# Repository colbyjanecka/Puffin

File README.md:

<p align="center">

<br><br></p>

# Puffin Keys - Mechanical Keyboard / MIDI Sequencer

*The Atlantic Puffin is not just any bird.*

It's a skilled flier, reaching speeds of 88km/h by flapping their wings up to 400 per minute.  They are also expert swimmers, diving up to 60 meters while using their wings to propel themselves through  water.

**Here, we have the Puffin of Mechanical Keyboards.**  

First, the Puffin Keys is an exceptional typer.  By utilizing low profile mechanical switches, it creates a fun and exception typing experience in a small portable package. 

Second, it serves as a powerful MIDI controller and sequencer that can communicate both wirelessly and the onboard TRS hardware jacks.

[**`Powered by Mania Synths`**](https://mania.fm/)

## Features

- Kailh Choc v1 Switches with Hotswap Sockets
- Per-Key RGB Backlighting with SK6812 LEDs
- 2 x TRS Type-A MIDI Jacks (In and Out)
- 3000 mAh LIPO Battery
- Bluetooth 5 and BLE 
- Dual 32bit Xtensa LX7 cores
- 0.91" OLED Display*
- Future Expansion Capabilities

**The screen can be replaced with alternative I2C input/output modules such as knobs, sensors, or CV ports.*

## PCB

<p align="center">
<br><h3> Front</h3>

<br><h3> Back</h3>

<br><br></p>

## Layout

<p align="center">
<br><h3> Front</h3>

<br><h3> Back</h3>

<br><br></p>

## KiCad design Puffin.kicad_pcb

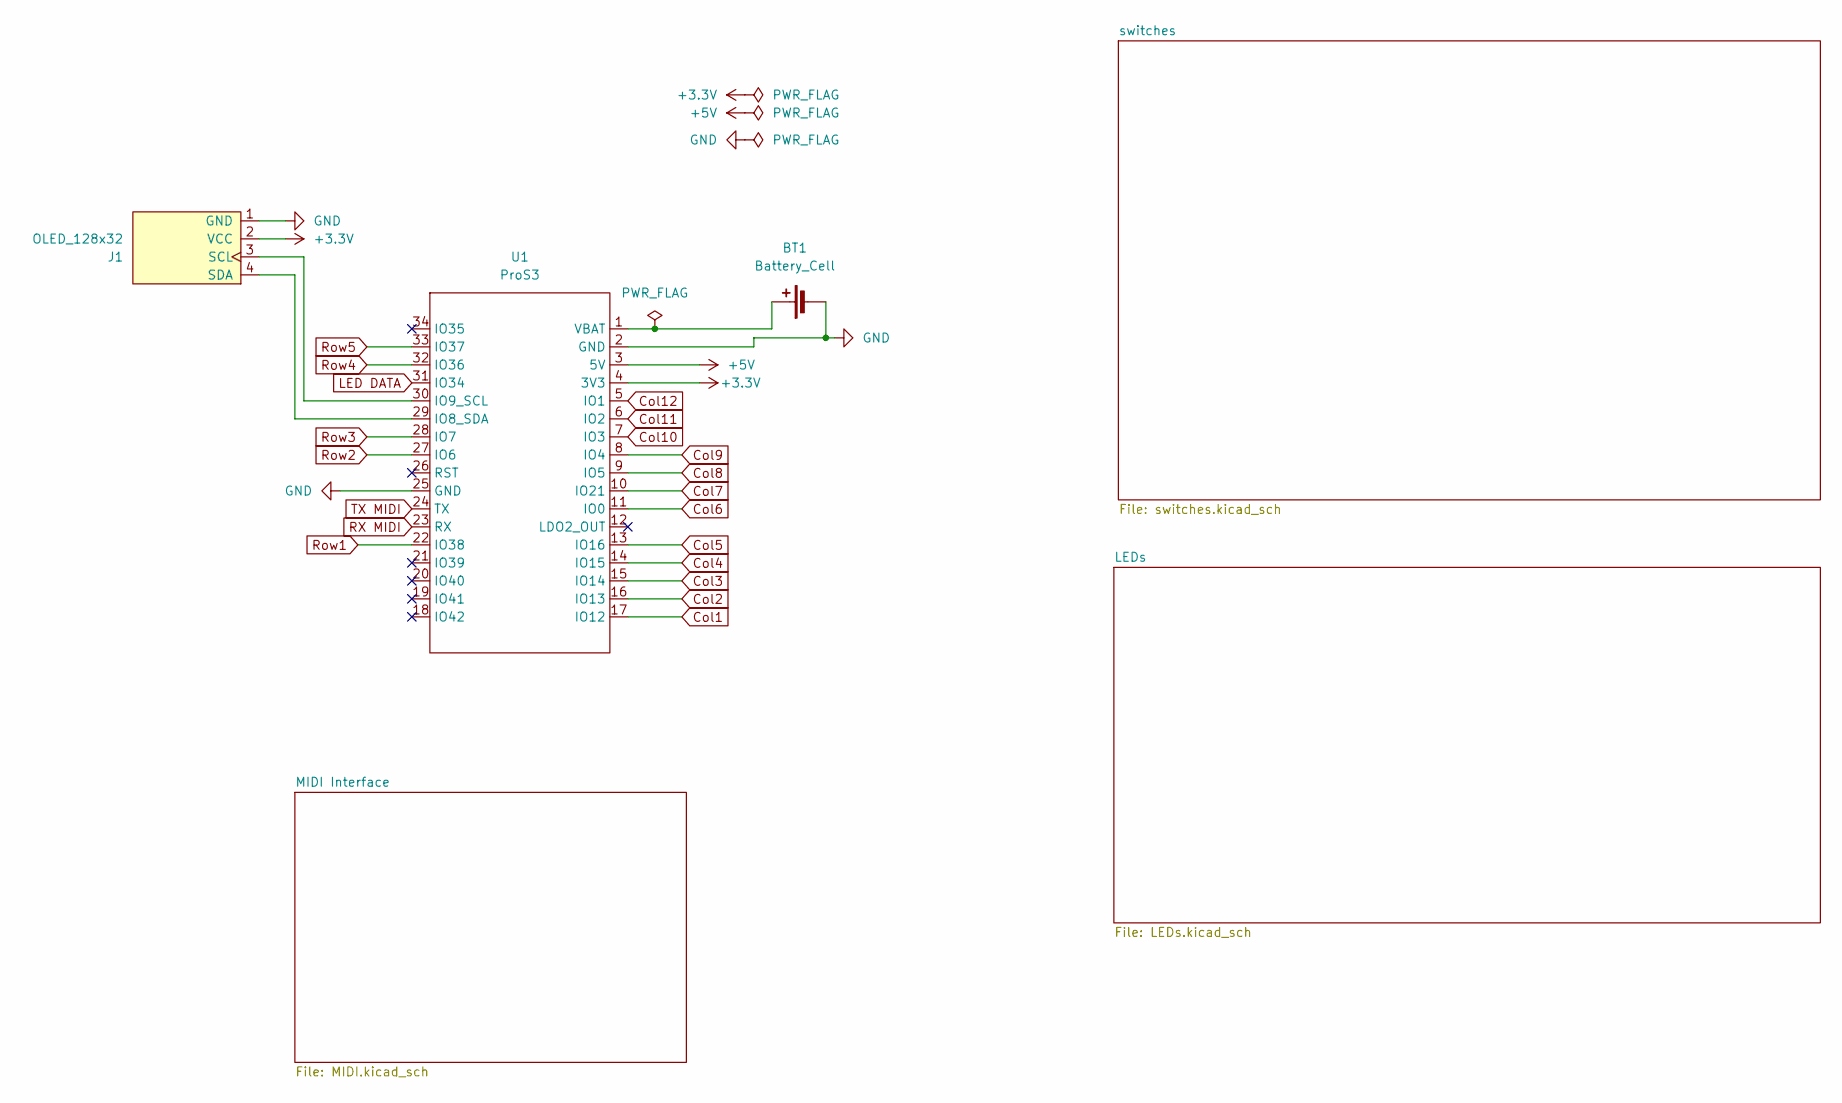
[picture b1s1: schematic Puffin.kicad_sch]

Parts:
BT1: Battery_Cell
J1: OLED_128x32
U1: ProS3; ProS3_TH

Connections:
+3.3V: J1.2 (VCC), U1.4 (3V3)
+5V: U1.3 (5V); also elsewhere on the board
Col1: U1.17 (IO12); also elsewhere on the board
Col2: U1.16 (IO13); also elsewhere on the board
Col3: U1.15 (IO14); also elsewhere on the board
Col4: U1.14 (IO15); also elsewhere on the board
Col5: U1.13 (IO16); also elsewhere on the board
Col6: U1.11 (IO0); also elsewhere on the board
Col7: U1.10 (IO21); also elsewhere on the board
Col8: U1.9 (IO5); also elsewhere on the board
Col9: U1.8 (IO4); also elsewhere on the board
Col10: U1.7 (IO3); also elsewhere on the board
Col11: U1.6 (IO2); also elsewhere on the board
Col12: U1.5 (IO1); also elsewhere on the board
GND: BT1.2 (-), J1.1 (GND), U1.2 (GND), U1.25 (GND); also elsewhere on the board
LED DATA: U1.31 (IO34); also elsewhere on the board
unnamed: BT1.1 (+), U1.1 (VBAT)
unnamed: J1.3 (SCL), U1.30 (IO9_SCL)
unnamed: J1.4 (SDA), U1.29 (IO8_SDA)
RX MIDI: U1.23 (RX); also elsewhere on the board
Row1: U1.22 (IO38); also elsewhere on the board
Row2: U1.27 (IO6); also elsewhere on the board
Row3: U1.28 (IO7); also elsewhere on the board
Row4: U1.32 (IO36); also elsewhere on the board
Row5: U1.33 (IO37); also elsewhere on the board
TX MIDI: U1.24 (TX); also elsewhere on the board

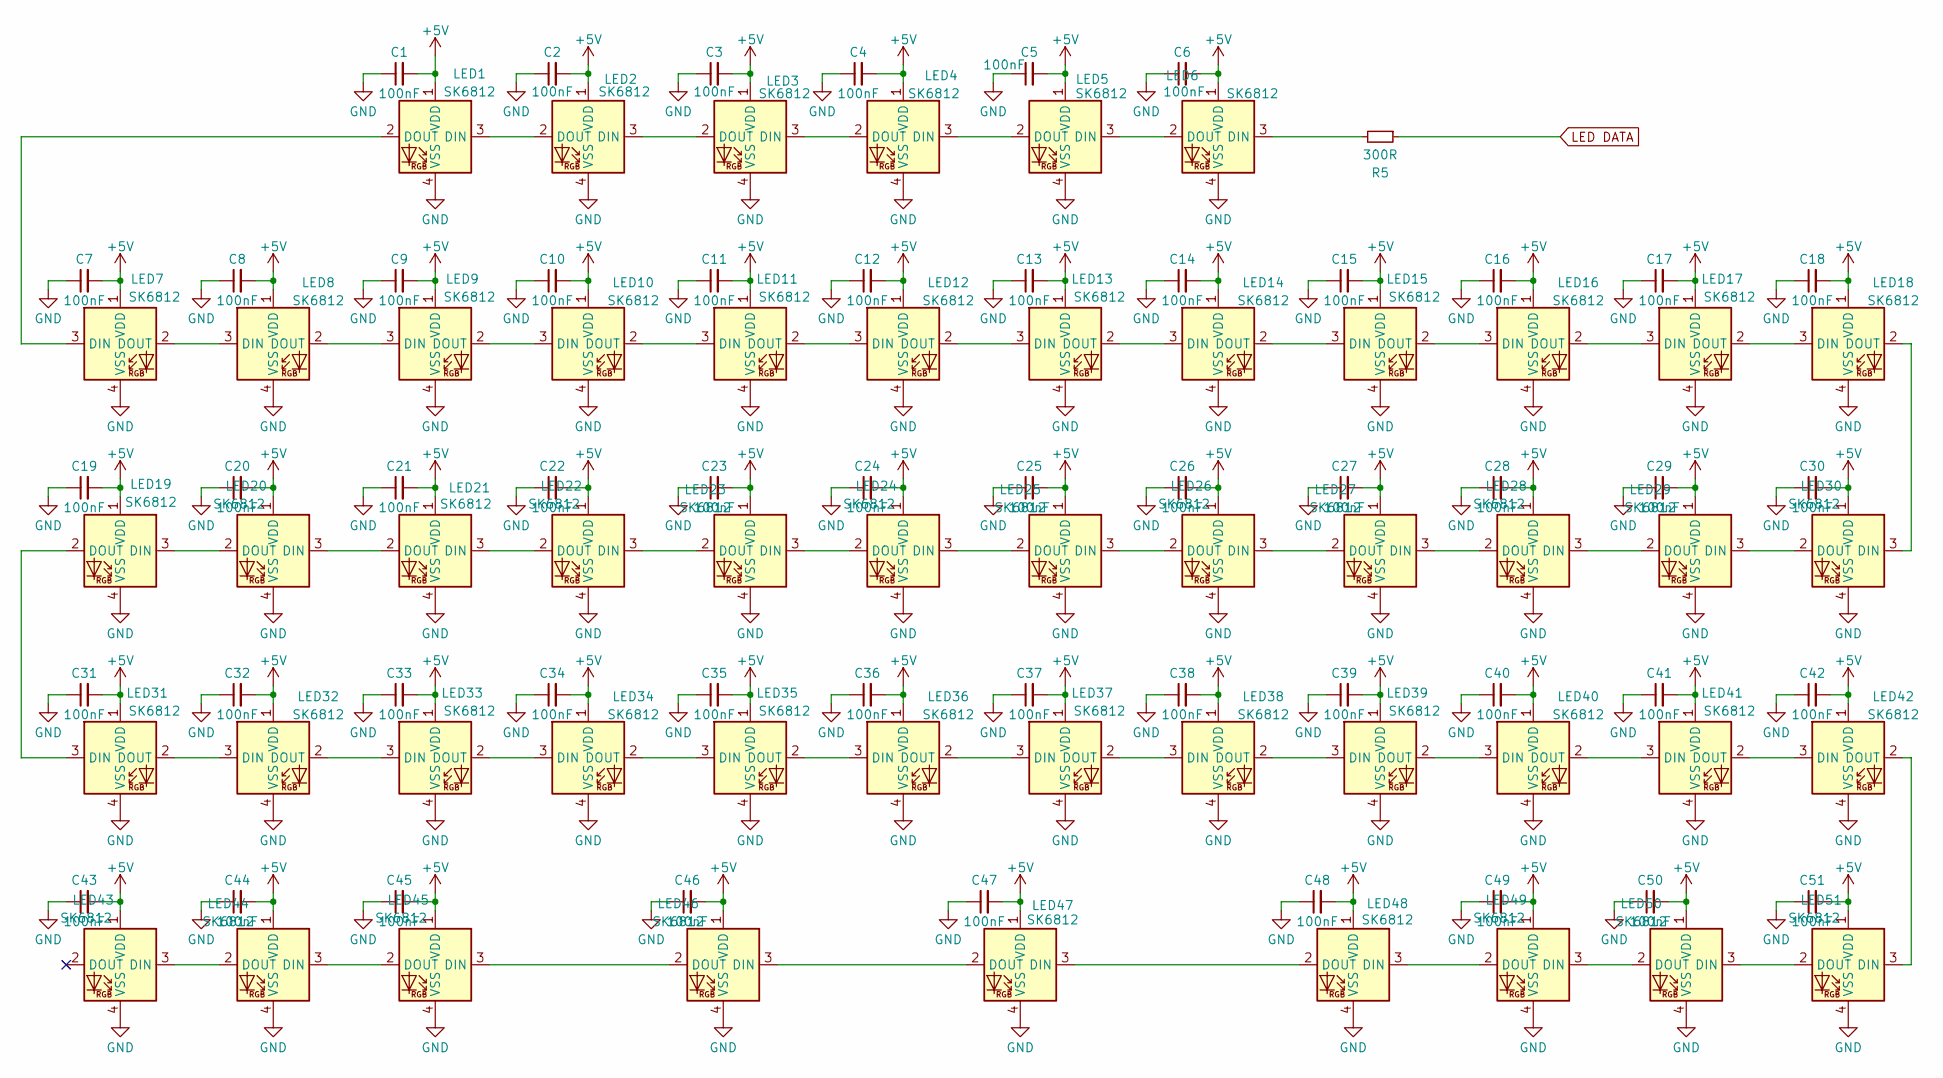
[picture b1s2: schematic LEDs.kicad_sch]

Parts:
C1, C2, C3, C4, C5, C6, C7, C8, C9, C10, C11, C12, C13, C14, C15, C16, C17, C18, C19, C20, C21, C22, C23, C24, C25, C26, C27, C28, C29, C30, C31, C32, C33, C34, C35, C36, C37, C38, C39, C40, C41, C42, C43, C44, C45, C46, C47, C48, C49, C50, C51: 100nF; C_0805
LED1, LED2, LED3, LED4, LED5, LED6, LED19, LED20, LED21, LED22, LED23, LED24, LED25, LED26, LED27, LED28, LED29, LED30, LED43, LED44, LED45, LED46, LED47, LED48, LED49, LED50, LED51: SK6812; LED_choc_6028R
LED7, LED8, LED9, LED10, LED11, LED12, LED13, LED14, LED15, LED16, LED17, LED18, LED31, LED32, LED33, LED34, LED35, LED36, LED37, LED38, LED39, LED40, LED41, LED42: SK6812; LED_choc_6028R-ROT
R5: 300R; R_0805_2012Metric

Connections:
+5V: C1.2, C2.2, C3.2, C4.2, C5.2, C6.2, C7.2, C8.2, C9.2, C10.2, C11.2, C12.2, C13.2, C14.2, C15.2, C16.2, C17.2, C18.2, C19.2, C20.2, C21.2, C22.2, C23.2, C24.2, C25.2, C26.2, C27.2, C28.2, C29.2, C30.2, C31.2, C32.2, C33.2, C34.2, C35.2, C36.2, C37.2, C38.2, C39.2, C40.2, C41.2, C42.2, C43.2, C44.2, C45.2, C46.2, C47.2, C48.2, C49.2, C50.2, C51.2, LED1.1 (VDD), LED2.1 (VDD), LED3.1 (VDD), LED4.1 (VDD), LED5.1 (VDD), LED6.1 (VDD), LED7.1 (VDD), LED8.1 (VDD), LED9.1 (VDD), LED10.1 (VDD), LED11.1 (VDD), LED12.1 (VDD), LED13.1 (VDD), LED14.1 (VDD), LED15.1 (VDD), LED16.1 (VDD), LED17.1 (VDD), LED18.1 (VDD), LED19.1 (VDD), LED20.1 (VDD), LED21.1 (VDD), LED22.1 (VDD), LED23.1 (VDD), LED24.1 (VDD), LED25.1 (VDD), LED26.1 (VDD), LED27.1 (VDD), LED28.1 (VDD), LED29.1 (VDD), LED30.1 (VDD), LED31.1 (VDD), LED32.1 (VDD), LED33.1 (VDD), LED34.1 (VDD), LED35.1 (VDD), LED36.1 (VDD), LED37.1 (VDD), LED38.1 (VDD), LED39.1 (VDD), LED40.1 (VDD), LED41.1 (VDD), LED42.1 (VDD), LED43.1 (VDD), LED44.1 (VDD), LED45.1 (VDD), LED46.1 (VDD), LED47.1 (VDD), LED48.1 (VDD), LED49.1 (VDD), LED50.1 (VDD), LED51.1 (VDD); also elsewhere on the board
GND: C1.1, C2.1, C3.1, C4.1, C5.1, C6.1, C7.1, C8.1, C9.1, C10.1, C11.1, C12.1, C13.1, C14.1, C15.1, C16.1, C17.1, C18.1, C19.1, C20.1, C21.1, C22.1, C23.1, C24.1, C25.1, C26.1, C27.1, C28.1, C29.1, C30.1, C31.1, C32.1, C33.1, C34.1, C35.1, C36.1, C37.1, C38.1, C39.1, C40.1, C41.1, C42.1, C43.1, C44.1, C45.1, C46.1, C47.1, C48.1, C49.1, C50.1, C51.1, LED1.4 (VSS), LED2.4 (VSS), LED3.4 (VSS), LED4.4 (VSS), LED5.4 (VSS), LED6.4 (VSS), LED7.4 (VSS), LED8.4 (VSS), LED9.4 (VSS), LED10.4 (VSS), LED11.4 (VSS), LED12.4 (VSS), LED13.4 (VSS), LED14.4 (VSS), LED15.4 (VSS), LED16.4 (VSS), LED17.4 (VSS), LED18.4 (VSS), LED19.4 (VSS), LED20.4 (VSS), LED21.4 (VSS), LED22.4 (VSS), LED23.4 (VSS), LED24.4 (VSS), LED25.4 (VSS), LED26.4 (VSS), LED27.4 (VSS), LED28.4 (VSS), LED29.4 (VSS), LED30.4 (VSS), LED31.4 (VSS), LED32.4 (VSS), LED33.4 (VSS), LED34.4 (VSS), LED35.4 (VSS), LED36.4 (VSS), LED37.4 (VSS), LED38.4 (VSS), LED39.4 (VSS), LED40.4 (VSS), LED41.4 (VSS), LED42.4 (VSS), LED43.4 (VSS), LED44.4 (VSS), LED45.4 (VSS), LED46.4 (VSS), LED47.4 (VSS), LED48.4 (VSS), LED49.4 (VSS), LED50.4 (VSS), LED51.4 (VSS); also elsewhere on the board
LED DATA: R5.1; also elsewhere on the board
unnamed: LED1.3 (DIN), LED2.2 (DOUT)
unnamed: LED1.2 (DOUT), LED7.3 (DIN)
unnamed: LED2.3 (DIN), LED3.2 (DOUT)
unnamed: LED3.3 (DIN), LED4.2 (DOUT)
unnamed: LED4.3 (DIN), LED5.2 (DOUT)
unnamed: LED5.3 (DIN), LED6.2 (DOUT)
unnamed: LED6.3 (DIN), R5.2
unnamed: LED7.2 (DOUT), LED8.3 (DIN)
unnamed: LED8.2 (DOUT), LED9.3 (DIN)
unnamed: LED9.2 (DOUT), LED10.3 (DIN)
unnamed: LED10.2 (DOUT), LED11.3 (DIN)
unnamed: LED11.2 (DOUT), LED12.3 (DIN)
unnamed: LED12.2 (DOUT), LED13.3 (DIN)
unnamed: LED13.2 (DOUT), LED14.3 (DIN)
unnamed: LED14.2 (DOUT), LED15.3 (DIN)
unnamed: LED15.2 (DOUT), LED16.3 (DIN)
unnamed: LED16.2 (DOUT), LED17.3 (DIN)
unnamed: LED17.2 (DOUT), LED18.3 (DIN)
unnamed: LED18.2 (DOUT), LED30.3 (DIN)
unnamed: LED19.3 (DIN), LED20.2 (DOUT)
unnamed: LED19.2 (DOUT), LED31.3 (DIN)
unnamed: LED20.3 (DIN), LED21.2 (DOUT)
unnamed: LED21.3 (DIN), LED22.2 (DOUT)
unnamed: LED22.3 (DIN), LED23.2 (DOUT)
unnamed: LED23.3 (DIN), LED24.2 (DOUT)
unnamed: LED24.3 (DIN), LED25.2 (DOUT)
unnamed: LED25.3 (DIN), LED26.2 (DOUT)
unnamed: LED26.3 (DIN), LED27.2 (DOUT)
unnamed: LED27.3 (DIN), LED28.2 (DOUT)
unnamed: LED28.3 (DIN), LED29.2 (DOUT)
unnamed: LED29.3 (DIN), LED30.2 (DOUT)
unnamed: LED31.2 (DOUT), LED32.3 (DIN)
unnamed: LED32.2 (DOUT), LED33.3 (DIN)
unnamed: LED33.2 (DOUT), LED34.3 (DIN)
unnamed: LED34.2 (DOUT), LED35.3 (DIN)
unnamed: LED35.2 (DOUT), LED36.3 (DIN)
unnamed: LED36.2 (DOUT), LED37.3 (DIN)
unnamed: LED37.2 (DOUT), LED38.3 (DIN)
unnamed: LED38.2 (DOUT), LED39.3 (DIN)
unnamed: LED39.2 (DOUT), LED40.3 (DIN)
unnamed: LED40.2 (DOUT), LED41.3 (DIN)
unnamed: LED41.2 (DOUT), LED42.3 (DIN)
unnamed: LED42.2 (DOUT), LED51.3 (DIN)
unnamed: LED43.3 (DIN), LED44.2 (DOUT)
unnamed: LED44.3 (DIN), LED45.2 (DOUT)
unnamed: LED45.3 (DIN), LED46.2 (DOUT)
unnamed: LED46.3 (DIN), LED47.2 (DOUT)
unnamed: LED47.3 (DIN), LED48.2 (DOUT)
unnamed: LED48.3 (DIN), LED49.2 (DOUT)
unnamed: LED49.3 (DIN), LED50.2 (DOUT)
unnamed: LED50.3 (DIN), LED51.2 (DOUT)

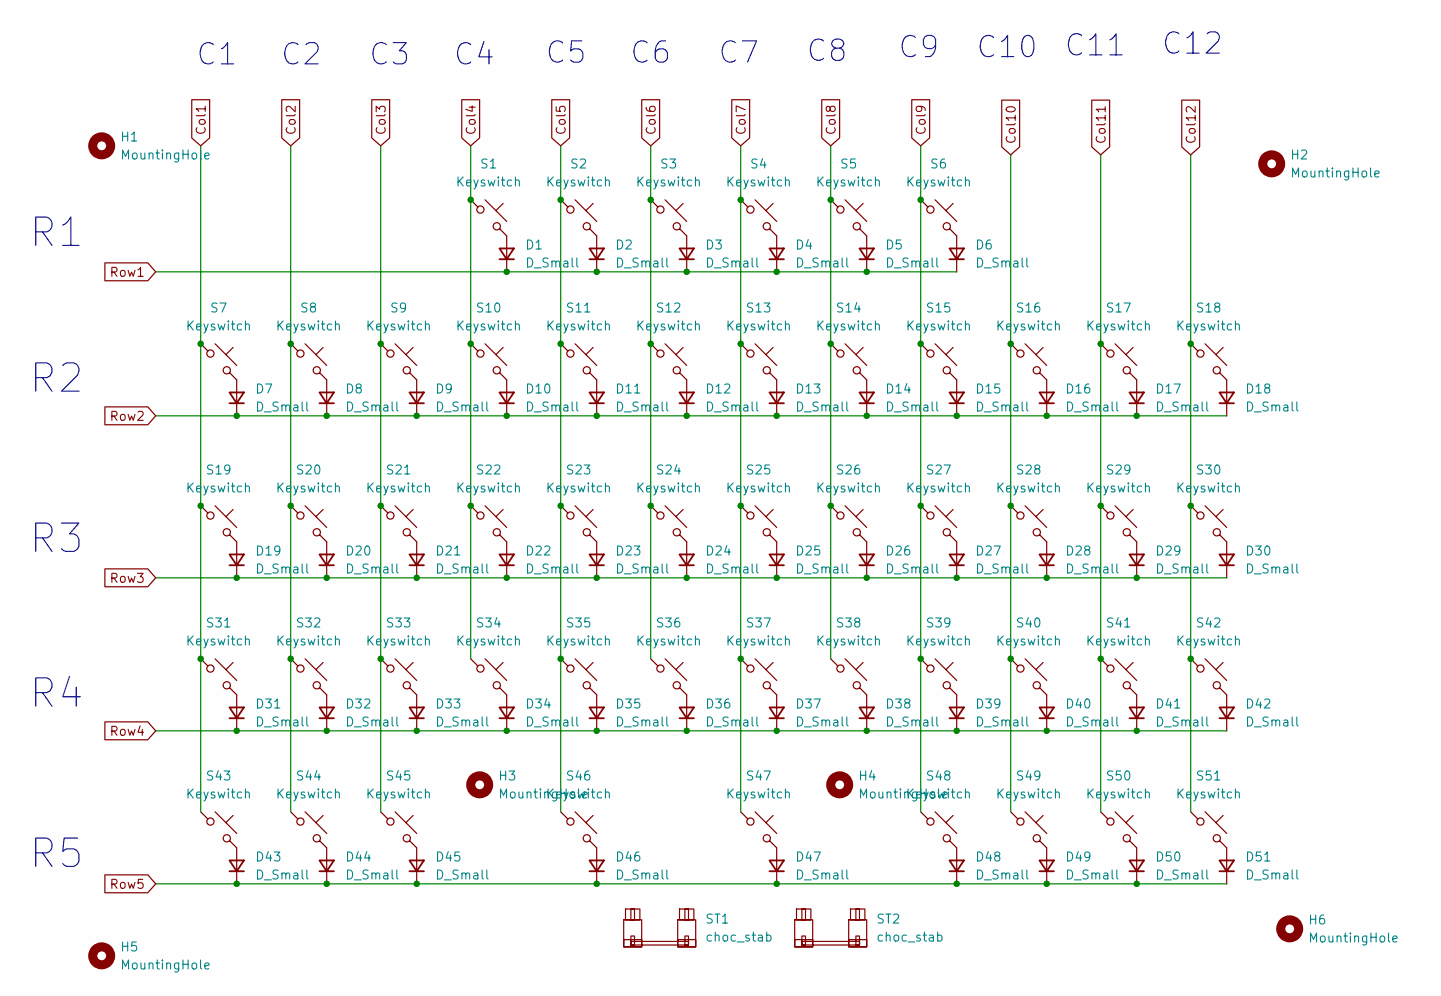
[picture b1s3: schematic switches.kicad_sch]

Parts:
D1, D2, D3, D4, D5, D6, D7, D8, D9, D10, D11, D12, D13, D14, D15, D16, D17, D18, D19, D20, D21, D22, D23, D24, D25, D26, D27, D28, D29, D30, D31, D32, D33, D34, D35, D36, D37, D38, D39, D40, D41, D42, D43, D44, D45, D46, D47, D48, D49, D50, D51: D_Small; D_SOD-323_HandSoldering
H1, H2, H3, H4, H5, H6: MountingHole; MountingHole_2.2mm_M2
S1, S2, S3, S4, S5, S6, S7, S8, S9, S10, S11, S12, S13, S14, S15, S16, S17, S18, S19, S20, S21, S22, S23, S24, S25, S26, S27, S28, S29, S30, S31, S32, S33, S34, S35, S36, S37, S38, S39, S40, S41, S42, S43, S44, S45, S46, S47, S48, S49, S50, S51: Keyswitch; SW_Hotswap_Kailh_Choc_V1_1.00u
ST1, ST2: choc_stab; STAB_choc_2u

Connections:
Col1: S7.1, S19.1, S31.1, S43.1; also elsewhere on the board
Col2: S8.1, S20.1, S32.1, S44.1; also elsewhere on the board
Col3: S9.1, S21.1, S33.1, S45.1; also elsewhere on the board
Col4: S1.1, S10.1, S22.1, S34.1; also elsewhere on the board
Col5: S2.1, S11.1, S23.1, S35.1, S46.1; also elsewhere on the board
Col6: S3.1, S12.1, S24.1, S36.1; also elsewhere on the board
Col7: S4.1, S13.1, S25.1, S37.1, S47.1; also elsewhere on the board
Col8: S5.1, S14.1, S26.1, S38.1; also elsewhere on the board
Col9: S6.1, S15.1, S27.1, S39.1, S48.1; also elsewhere on the board
Col10: S16.1, S28.1, S40.1, S49.1; also elsewhere on the board
Col11: S17.1, S29.1, S41.1, S50.1; also elsewhere on the board
Col12: S18.1, S30.1, S42.1, S51.1; also elsewhere on the board
unnamed: D1.2 (A), S1.2
unnamed: D2.2 (A), S2.2
unnamed: D3.2 (A), S3.2
unnamed: D4.2 (A), S4.2
unnamed: D5.2 (A), S5.2
unnamed: D6.2 (A), S6.2
unnamed: D7.2 (A), S7.2
unnamed: D8.2 (A), S8.2
unnamed: D9.2 (A), S9.2
unnamed: D10.2 (A), S10.2
unnamed: D11.2 (A), S11.2
unnamed: D12.2 (A), S12.2
unnamed: D13.2 (A), S13.2
unnamed: D14.2 (A), S14.2
unnamed: D15.2 (A), S15.2
unnamed: D16.2 (A), S16.2
unnamed: D17.2 (A), S17.2
unnamed: D18.2 (A), S18.2
unnamed: D19.2 (A), S19.2
unnamed: D20.2 (A), S20.2
unnamed: D21.2 (A), S21.2
unnamed: D22.2 (A), S22.2
unnamed: D23.2 (A), S23.2
unnamed: D24.2 (A), S24.2
unnamed: D25.2 (A), S25.2
unnamed: D26.2 (A), S26.2
unnamed: D27.2 (A), S27.2
unnamed: D28.2 (A), S28.2
unnamed: D29.2 (A), S29.2
unnamed: D30.2 (A), S30.2
unnamed: D31.2 (A), S31.2
unnamed: D32.2 (A), S32.2
unnamed: D33.2 (A), S33.2
unnamed: D34.2 (A), S34.2
unnamed: D35.2 (A), S35.2
unnamed: D36.2 (A), S36.2
unnamed: D37.2 (A), S37.2
unnamed: D38.2 (A), S38.2
unnamed: D39.2 (A), S39.2
unnamed: D40.2 (A), S40.2
unnamed: D41.2 (A), S41.2
unnamed: D42.2 (A), S42.2
unnamed: D43.2 (A), S43.2
unnamed: D44.2 (A), S44.2
unnamed: D45.2 (A), S45.2
unnamed: D46.2 (A), S46.2
unnamed: D47.2 (A), S47.2
unnamed: D48.2 (A), S48.2
unnamed: D49.2 (A), S49.2
unnamed: D50.2 (A), S50.2
unnamed: D51.2 (A), S51.2
Row1: D1.1 (K), D2.1 (K), D3.1 (K), D4.1 (K), D5.1 (K), D6.1 (K); also elsewhere on the board
Row2: D7.1 (K), D8.1 (K), D9.1 (K), D10.1 (K), D11.1 (K), D12.1 (K), D13.1 (K), D14.1 (K), D15.1 (K), D16.1 (K), D17.1 (K), D18.1 (K); also elsewhere on the board
Row3: D19.1 (K), D20.1 (K), D21.1 (K), D22.1 (K), D23.1 (K), D24.1 (K), D25.1 (K), D26.1 (K), D27.1 (K), D28.1 (K), D29.1 (K), D30.1 (K); also elsewhere on the board
Row4: D31.1 (K), D32.1 (K), D33.1 (K), D34.1 (K), D35.1 (K), D36.1 (K), D37.1 (K), D38.1 (K), D39.1 (K), D40.1 (K), D41.1 (K), D42.1 (K); also elsewhere on the board
Row5: D43.1 (K), D44.1 (K), D45.1 (K), D46.1 (K), D47.1 (K), D48.1 (K), D49.1 (K), D50.1 (K), D51.1 (K); also elsewhere on the board

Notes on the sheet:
C10
C11
C12

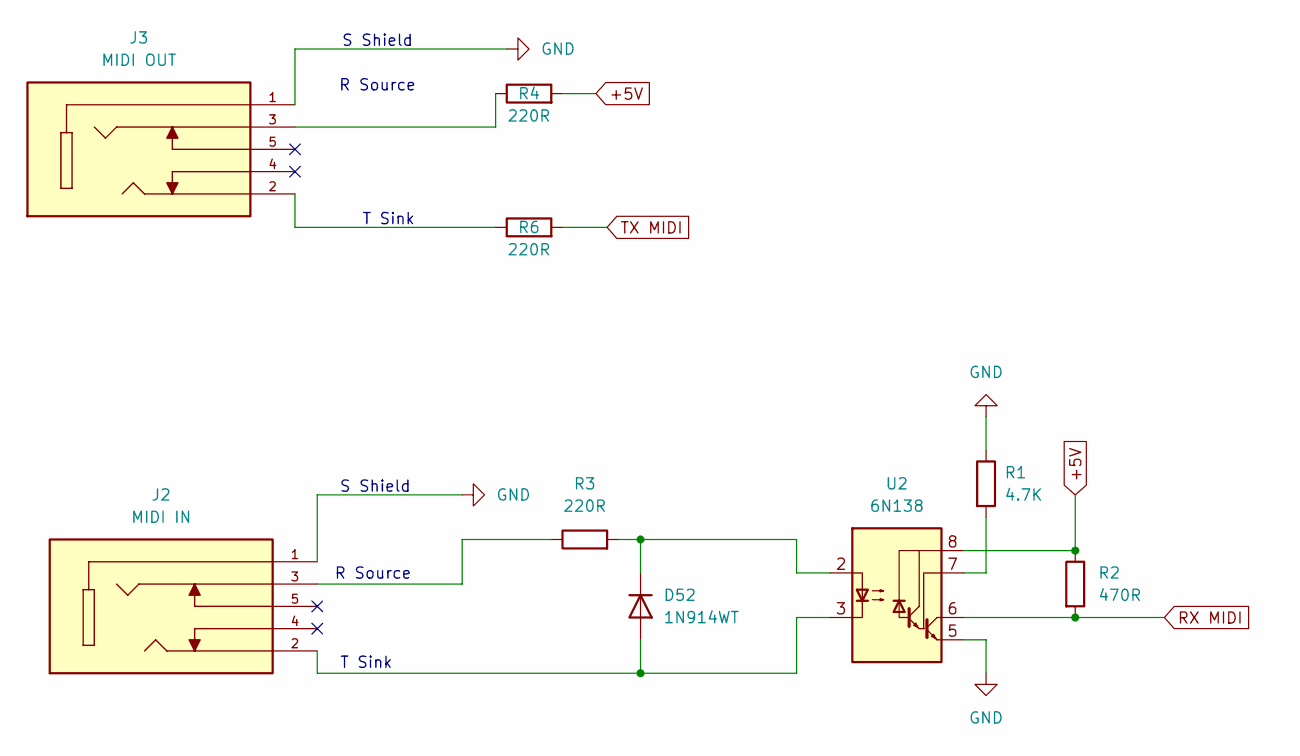
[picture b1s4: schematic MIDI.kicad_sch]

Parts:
D52: 1N914WT; D_SOD-123
J2: MIDI IN; CUI_SJ1-3515; MPN SJ2-3593A-SMT-TR
J3: MIDI OUT; CUI_SJ1-3515; MPN SJ2-3593A-SMT-TR
R1: 4.7K; R_0805_2012Metric
R2: 470R; R_0805_2012Metric
R3, R4, R6: 220R; R_0805_2012Metric
U2: 6N138; DIP762W50P254L1018H450Q8

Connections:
+5V: R2.1, R4.2, U2.8 (VCC); also elsewhere on the board
GND: J2.1, J3.1, R1.1, U2.5 (GND); also elsewhere on the board
unnamed: D52.2 (A), J2.2, U2.3 (C2)
unnamed: D52.1 (K), R3.2, U2.2 (C1)
unnamed: J2.3, R3.1
unnamed: J3.2, R6.1
unnamed: J3.3, R4.1
unnamed: R1.2, U2.7 (VO1)
RX MIDI: R2.2, U2.6 (VO2); also elsewhere on the board
TX MIDI: R6.2; also elsewhere on the board

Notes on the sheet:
T Sink
R Source
S Shield

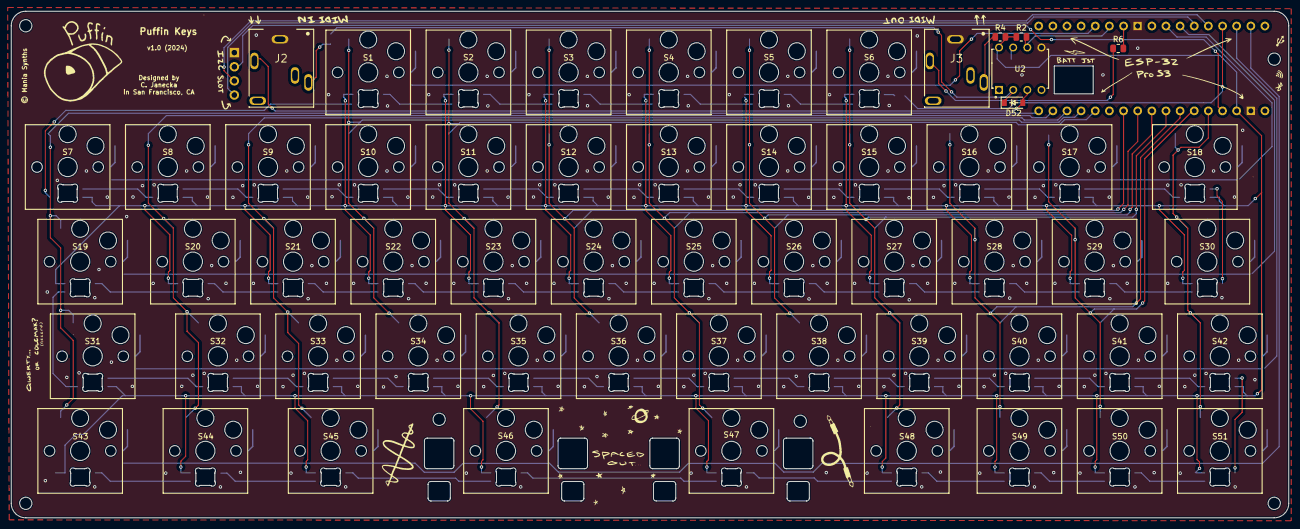
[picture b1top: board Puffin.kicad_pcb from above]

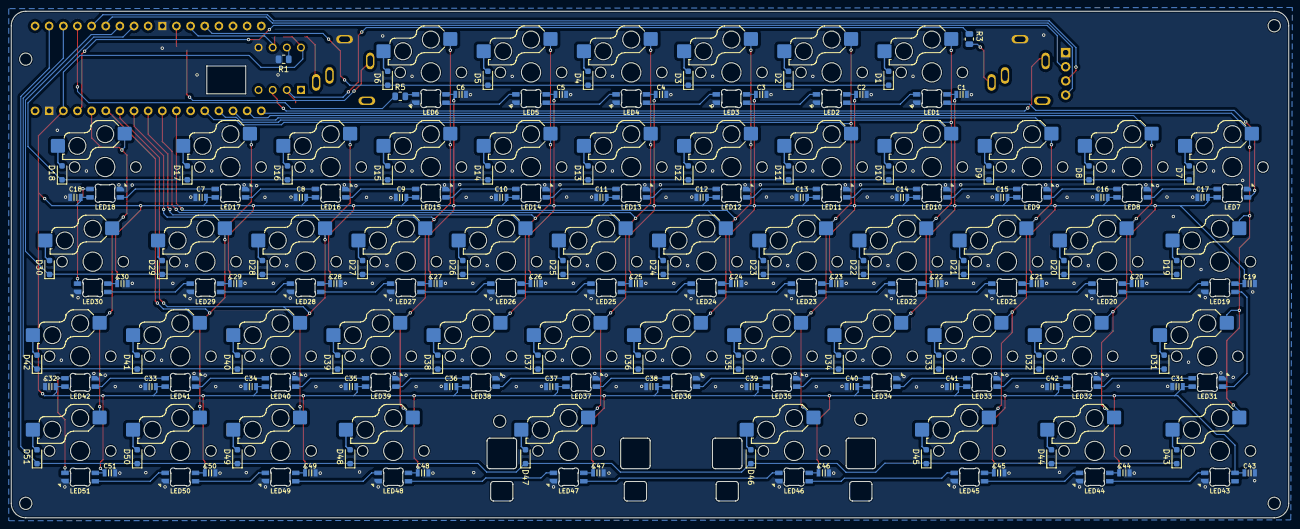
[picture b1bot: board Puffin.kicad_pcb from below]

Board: 2 copper layers, 229.5 x 91.0 mm, 225 parts (156 on the bottom side), 133 nets.

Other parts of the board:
PuffinHead: LOGO

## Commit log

2024-07-23 changed capacitor size
2025-03-28 updated info
2025-03-28 cleaned up repo
2025-03-28 clean up
2025-03-28 added firmware repo

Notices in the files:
Puffin.kicad_pcb:
© Mania Synths
